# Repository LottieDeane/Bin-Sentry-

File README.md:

# Bin-Sentry-
Open source designs and code for the bin sentry

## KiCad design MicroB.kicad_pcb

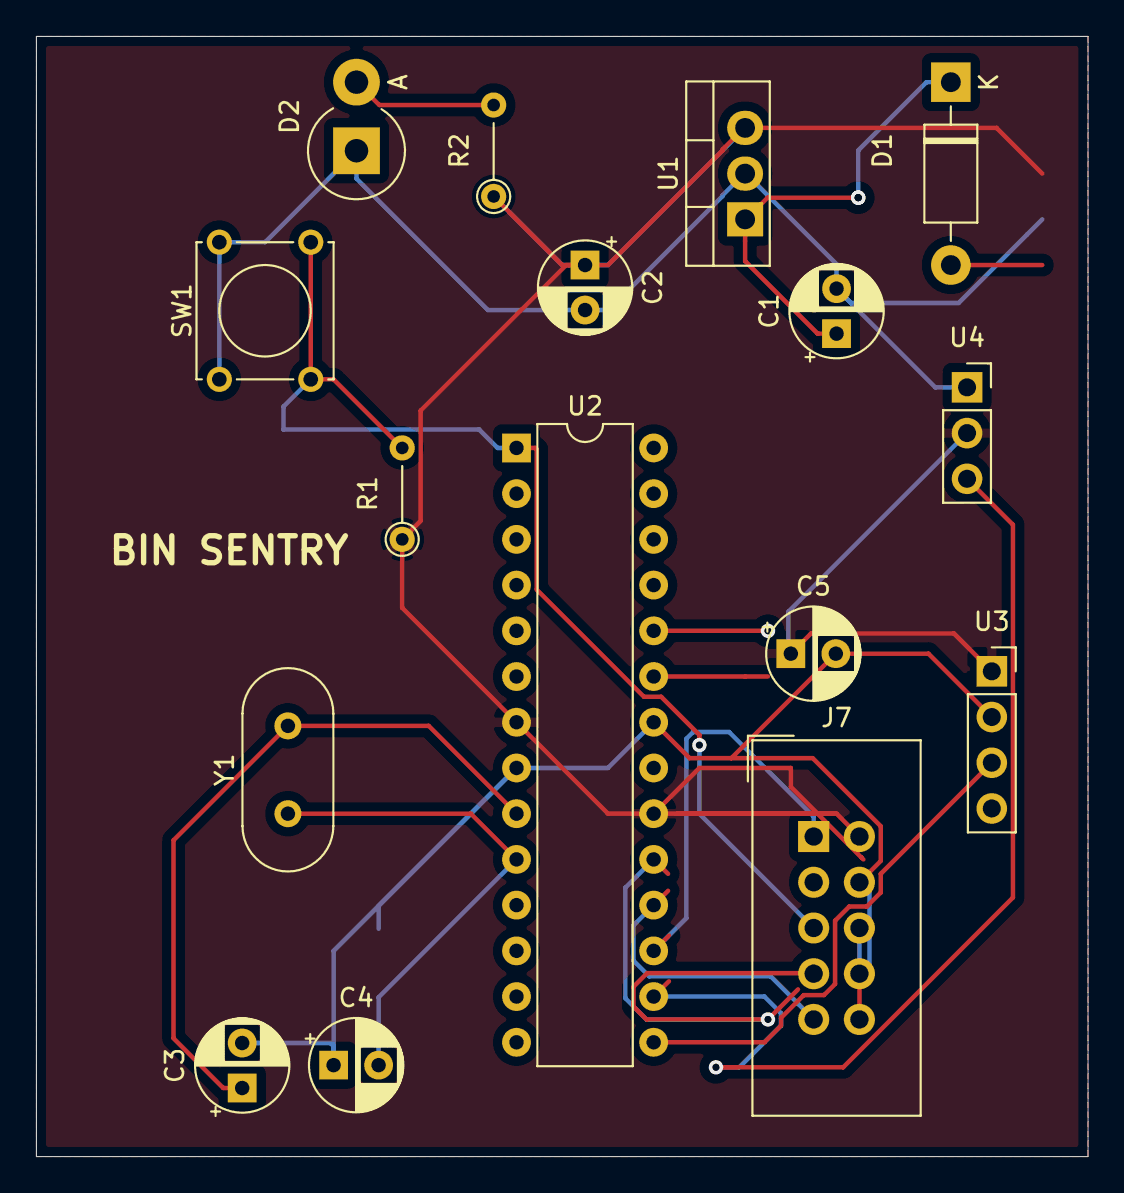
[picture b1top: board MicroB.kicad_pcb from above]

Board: 2 copper layers, 58.4 x 62.2 mm, 16 parts (0 on the bottom side), 13 nets.

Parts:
C1: 100u; CP_Radial_D5.0mm_P2.50mm
C2: 22u; CP_Radial_D5.0mm_P2.50mm
C3, C4: 22p; CP_Radial_D5.0mm_P2.50mm
C5: C; CP_Radial_D5.0mm_P2.50mm
D1: 1N4007; D_DO-41_SOD81_P10.16mm_Horizontal
D2: LED_ALT; D_DO-201_P3.81mm_Vertical_AnodeUp
J7: Conn_02x05_Counter_Clockwise; IDC-Header_2x05_P2.54mm_Vertical
R1: R; R_Axial_DIN0204_L3.6mm_D1.6mm_P5.08mm_Vertical
R2: 220; R_Axial_DIN0204_L3.6mm_D1.6mm_P5.08mm_Vertical
SW1: SW_Push; SW_Tactile_Straight_KSA0Axx1LFTR
U1: LM7805_TO220; TO-220-3_Vertical
U2: ATmega328P-PU; DIP-28_W7.62mm
U3: transmitter; PinSocket_1x04_P2.54mm_Vertical
U4: tilt; PinSocket_1x03_P2.54mm_Vertical
Y1: Crystal; Crystal_HC49-U_Vertical

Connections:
+5V: C5.1, J7.2, R1.1, U2.7, U2.20, U3.1, U4.2
GND: C1.2, C2.2, C3.2, C4.1, C5.2, D2.1, J7.4, J7.6, J7.8, J7.10, SW1.1, U1.2, U2.8, U2.22, U3.2, U4.1
MISO: J7.9, U2.18
MOSI: J7.1, U2.17
unnamed: C1.1, D1.1, U1.1
unnamed: C2.1, R2.1, U1.3
unnamed: D2.2, R2.2
unnamed: U2.15, U3.3
unnamed: U2.16, U4.3
RESET: J7.5, R1.2, SW1.2, U2.1
SCK: J7.7, U2.19
XTAL1: C3.1, U2.9, Y1.2
XTAL2: C4.2, U2.10, Y1.1

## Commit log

2021-06-20 Rename MicroB.kicad_pcb to BinSentryPCB.kicad_pcb
2021-06-20 Rename MicroB.pro to BinSentryPCBProject.pro
2021-06-20 Rename MicroB.sch to BinSentryPCBSchematic.sch
